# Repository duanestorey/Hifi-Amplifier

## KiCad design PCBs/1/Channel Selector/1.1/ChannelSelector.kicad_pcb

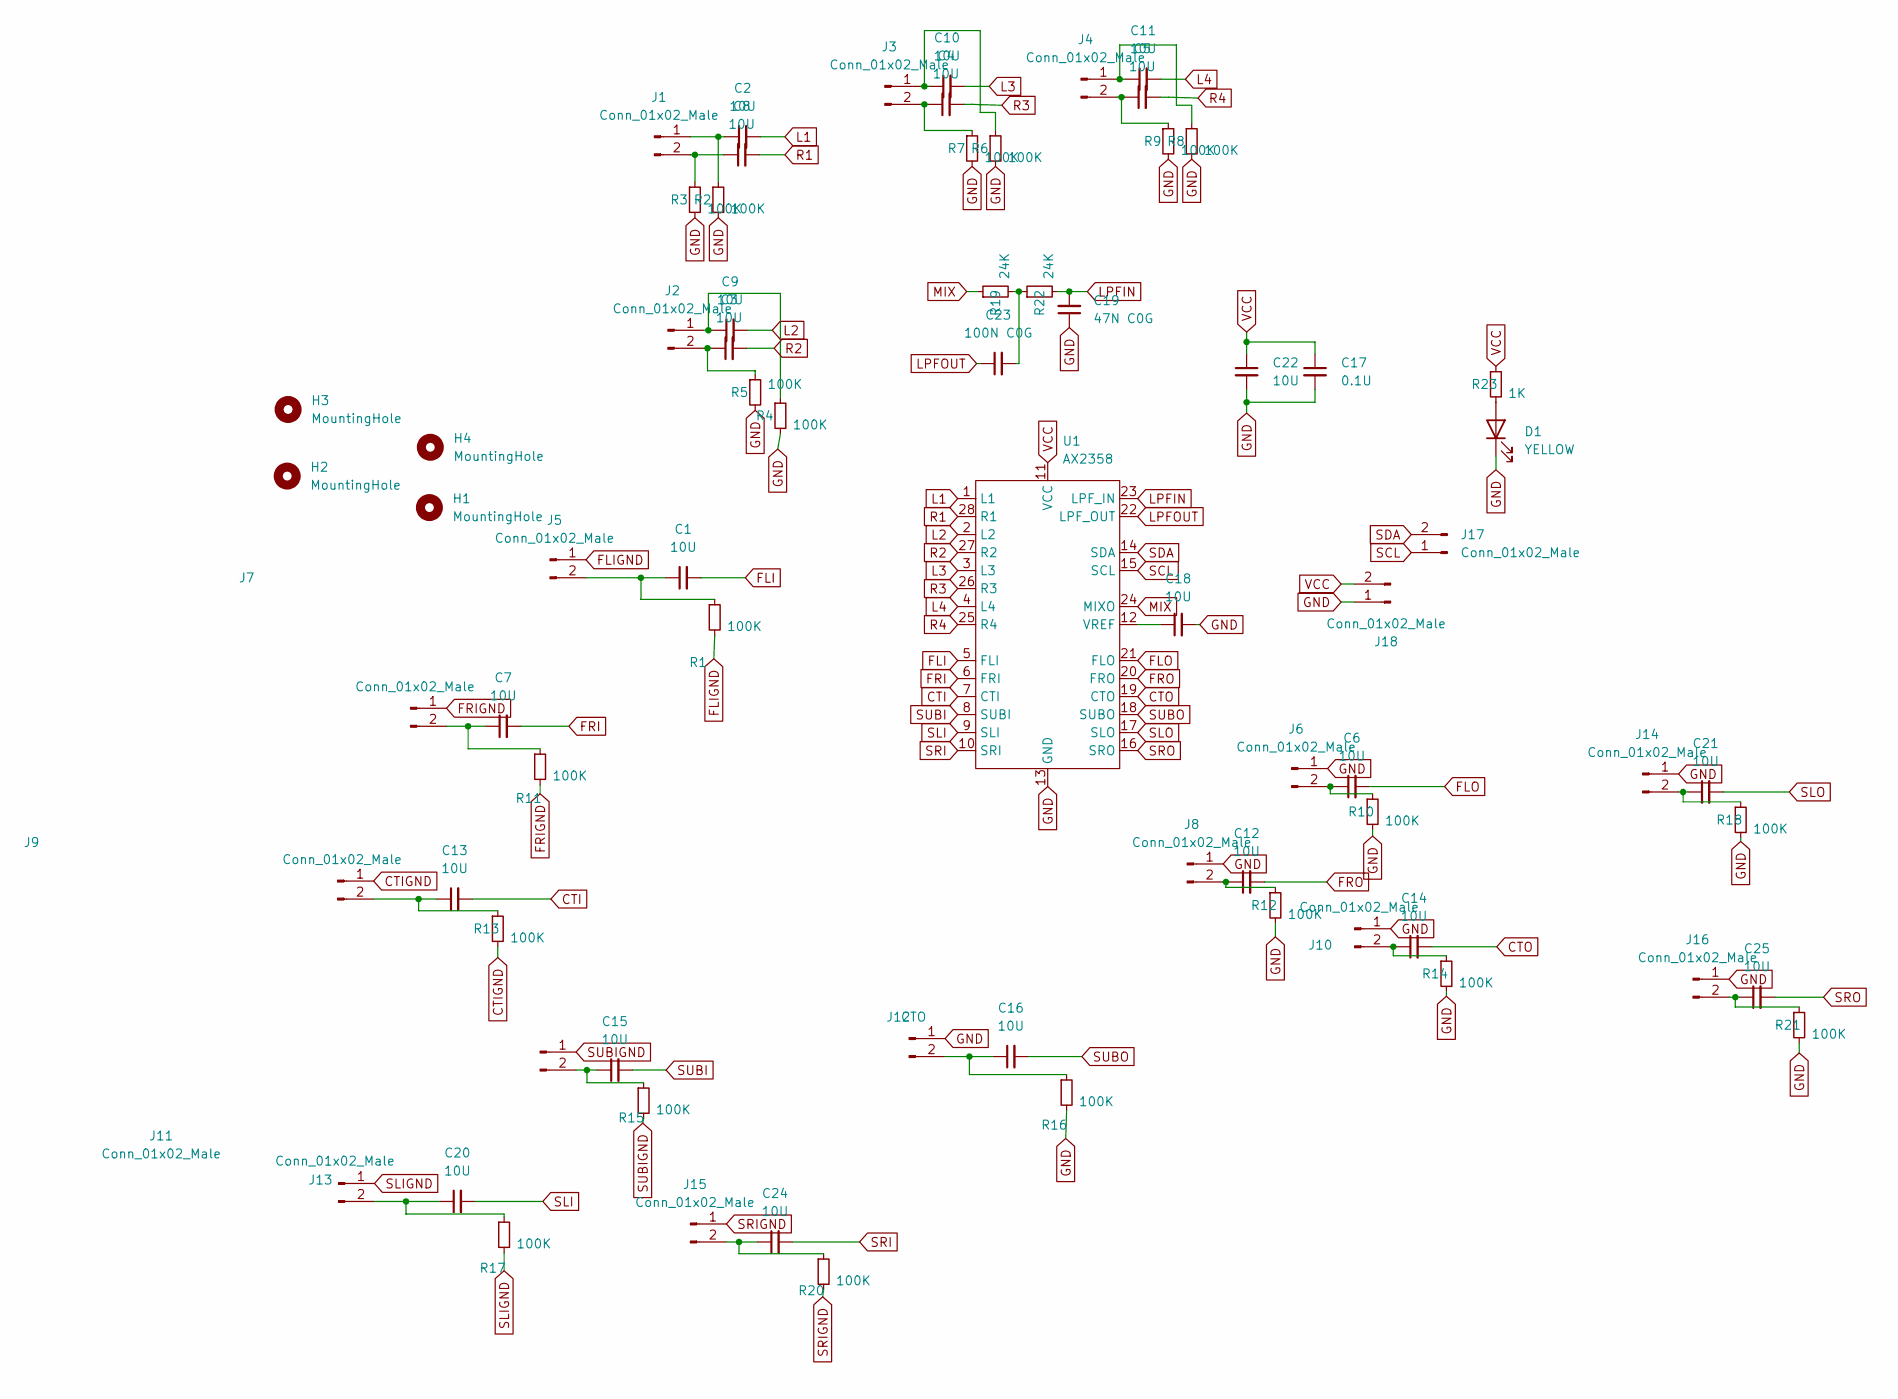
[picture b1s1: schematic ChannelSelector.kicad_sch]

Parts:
C1, C2, C3, C4, C5, C6, C7, C8, C9, C10, C11, C12, C13, C14, C15, C16, C20, C21, C24, C25: 10U; CP_Radial_D5.0mm_P2.50mm
C17: 0.1U; C_0805_2012Metric_Pad1.18x1.45mm_HandSolder
C18, C22: 10U; C_1206_3216Metric_Pad1.33x1.80mm_HandSolder
C19: 47N C0G; C_1206_3216Metric_Pad1.33x1.80mm_HandSolder
C23: 100N C0G; C_1206_3216Metric_Pad1.33x1.80mm_HandSolder
D1: YELLOW; LED_0805_2012Metric_Pad1.15x1.40mm_HandSolder
H1, H2, H3, H4: MountingHole; MountingHole_3.2mm_M3
J1, J2, J3, J4, J5, J6, J7, J8, J9, J10, J11, J13, J14, J15, J16, J17, J18: Conn_01x02_Male; JST_PH_B2B-PH-K_1x02_P2.00mm_Vertical
J12: CTO; JST_PH_B2B-PH-K_1x02_P2.00mm_Vertical
R1, R2, R3, R4, R5, R6, R7, R8, R9, R10, R11, R12, R13, R14, R15, R16, R17, R18, R20, R21: 100K; R_0805_2012Metric_Pad1.20x1.40mm_HandSolder
R19, R22: 24K; R_0805_2012Metric_Pad1.20x1.40mm_HandSolder
R23: 1K; R_0603_1608Metric_Pad0.98x0.95mm_HandSolder
U1: AX2358; SOIC-28W_7.5x18.7mm_P1.27mm

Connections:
CTI: C13.2, U1.7 (CTI)
CTIGND: J9.1, R13.2
CTO: C14.2, U1.19 (CTO)
FLI: C1.2, U1.5 (FLI)
FLIGND: J5.1, R1.2
FLO: C6.2, U1.21 (FLO)
FRI: C7.2, U1.6 (FRI)
FRIGND: J7.1, R11.2
FRO: C12.2, U1.20 (FRO)
GND: C17.2, C18.2, C19.1, C22.2, D1.1 (K), J6.1, J8.1, J10.1, J12.1, J14.1, J16.1, J18.1, R2.2, R3.2, R4.2, R5.2, R6.2, R7.2, R8.2, R9.2, R10.2, R12.2, R14.2, R16.2, R18.2, R21.2, U1.13 (GND)
L1: C2.2, U1.1 (L1)
L2: C9.2, U1.2 (L2)
L3: C10.2, U1.3 (L3)
L4: C11.2, U1.4 (L4)
LPFIN: C19.2, R22.2, U1.23 (LPF_IN)
LPFOUT: C23.1, U1.22 (LPF_OUT)
MIX: R19.1, U1.24 (MIXO)
unnamed: C23.2, R19.2, R22.1
unnamed: D1.2 (A), R23.2
unnamed: C2.1, J1.1, R2.1
unnamed: C8.1, J1.2, R3.1
unnamed: C9.1, J2.1, R4.1
unnamed: C3.1, J2.2, R5.1
unnamed: C10.1, J3.1, R6.1
unnamed: C4.1, J3.2, R7.1
unnamed: C11.1, J4.1, R8.1
unnamed: C5.1, J4.2, R9.1
unnamed: C1.1, J5.2, R1.1
unnamed: C6.1, J6.2, R10.1
unnamed: C7.1, J7.2, R11.1
unnamed: C12.1, J8.2, R12.1
unnamed: C13.1, J9.2, R13.1
unnamed: C14.1, J10.2, R14.1
unnamed: C15.1, J11.2, R15.1
unnamed: C16.1, J12.2, R16.1
unnamed: C20.1, J13.2, R17.1
unnamed: C21.1, J14.2, R18.1
unnamed: C24.1, J15.2, R20.1
unnamed: C25.1, J16.2, R21.1
unnamed: C18.1, U1.12 (VREF)
R1: C8.2, U1.28 (R1)
R2: C3.2, U1.27 (R2)
R3: C4.2, U1.26 (R3)
R4: C5.2, U1.25 (R4)
SCL: J17.1, U1.15 (SCL)
SDA: J17.2, U1.14 (SDA)
SLI: C20.2, U1.9 (SLI)
SLIGND: J13.1, R17.2
SLO: C21.2, U1.17 (SLO)
SRI: C24.2, U1.10 (SRI)
SRIGND: J15.1, R20.2
SRO: C25.2, U1.16 (SRO)
SUBI: C15.2, U1.8 (SUBI)
SUBIGND: J11.1, R15.2
SUBO: C16.2, U1.18 (SUBO)
VCC: C17.1, C22.1, J18.2, R23.1, U1.11 (VCC)

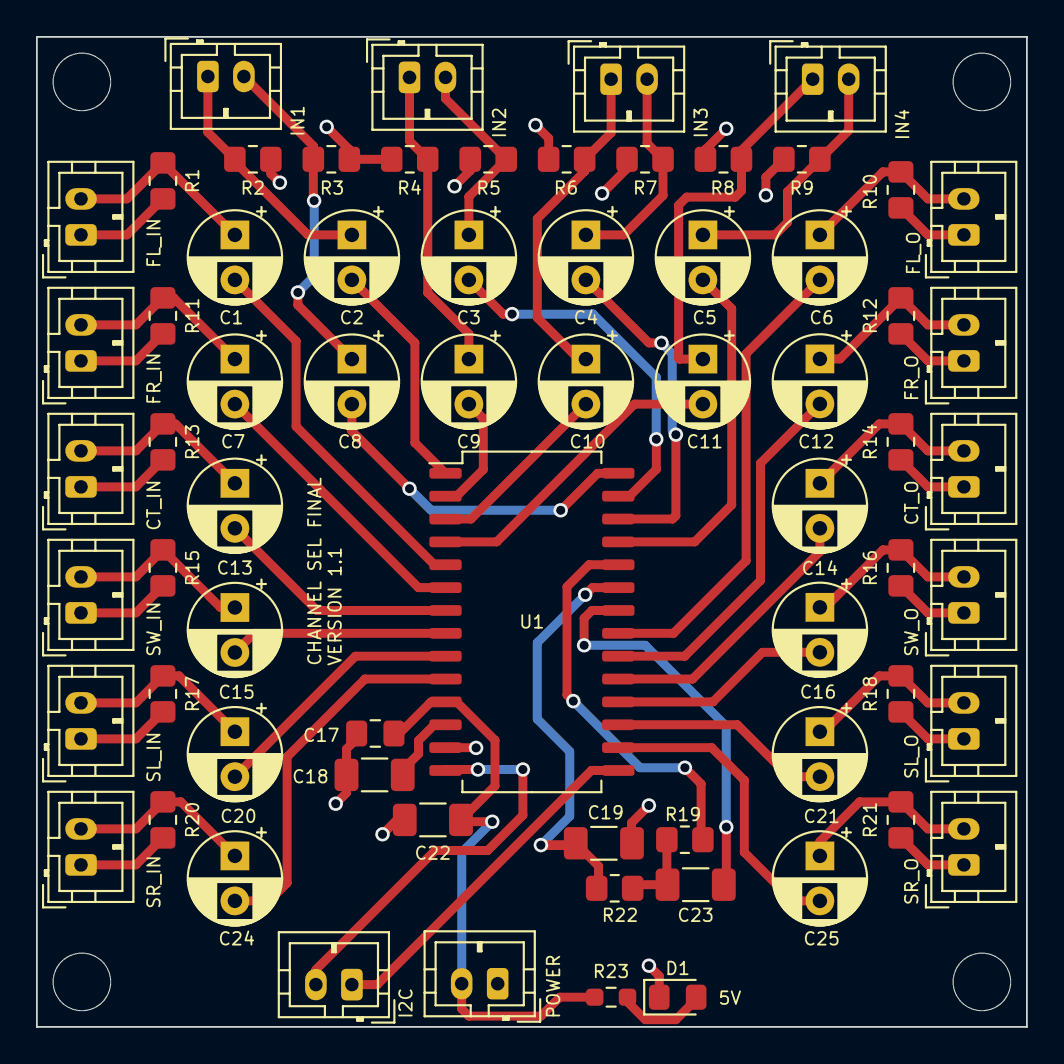
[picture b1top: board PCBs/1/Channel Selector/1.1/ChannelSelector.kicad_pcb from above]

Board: 2 copper layers, 55.0 x 55.0 mm, 72 parts (0 on the bottom side), 56 nets.

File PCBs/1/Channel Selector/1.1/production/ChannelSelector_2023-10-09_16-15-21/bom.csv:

Designator,Footprint,Quantity,Value,LCSC Part #
"C1, C10, C11, C12, C13, C14, C15, C16, C2, C20, C21, C24, C25, C3, C4, C5, C6, C7, C8, C9",CP_Radial_D5.0mm_P2.50mm,20,10U,
C17,0805,1,0.1U,
"C18, C22",1206,2,10U,
C19,1206,1,47N C0G,
C23,1206,1,100N C0G,
D1,0805,1,YELLOW,
"H1, H2, H3, H4",MountingHole_3.2mm_M3,4,MountingHole,
"J1, J10, J11, J13, J14, J15, J16, J17, J18, J2, J3, J4, J5, J6, J7, J8, J9",JST_PH_B2B-PH-K_1x02_P2.00mm_Vertical,17,Conn_01x02_Male,
J12,JST_PH_B2B-PH-K_1x02_P2.00mm_Vertical,1,CTO,
"R1, R10, R11, R12, R13, R14, R15, R16, R17, R18, R2, R20, R21, R3, R4, R5, R6, R7, R8, R9",0805,20,100K,
"R19, R22",0805,2,24K,
R23,0603,1,1K,
U1,SOIC-28W_7.5x18.7mm_P1.27mm,1,AX2358,

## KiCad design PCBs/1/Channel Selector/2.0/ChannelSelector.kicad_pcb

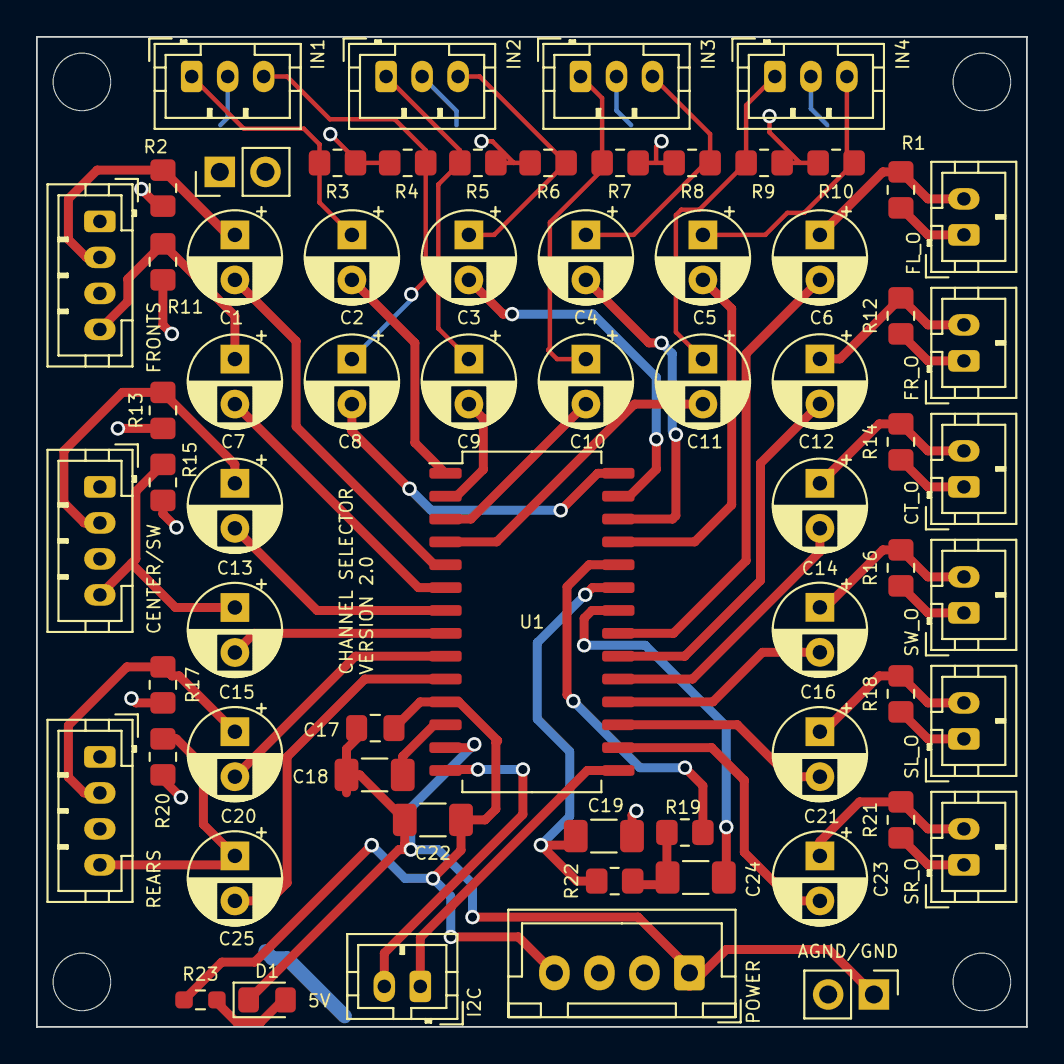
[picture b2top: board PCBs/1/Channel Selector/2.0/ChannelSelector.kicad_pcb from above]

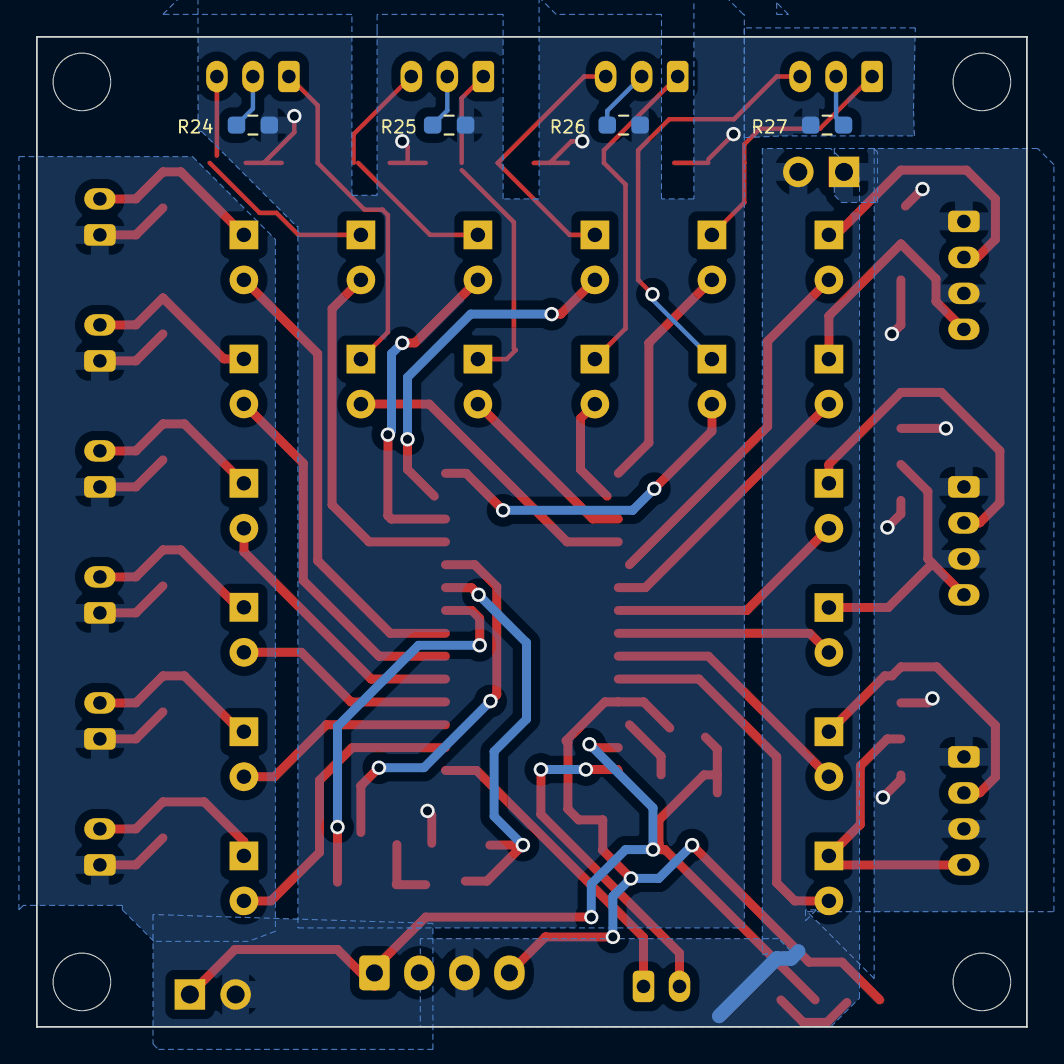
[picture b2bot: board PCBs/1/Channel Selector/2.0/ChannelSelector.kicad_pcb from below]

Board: 2 copper layers, 55.0 x 55.0 mm, 75 parts (4 on the bottom side), 56 nets.

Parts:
C1, C2, C3, C4, C5, C6, C7, C8, C9, C10, C11, C12, C13, C14, C15, C16, C20, C21, C23, C25: 10U; CP_Radial_D5.0mm_P2.50mm
C17: 0.1U; C_0805_2012Metric_Pad1.18x1.45mm_HandSolder
C18, C22: 10U; C_1206_3216Metric_Pad1.33x1.80mm_HandSolder
C19: 47N C0G; C_1206_3216Metric_Pad1.33x1.80mm_HandSolder
C24: 100N C0G; C_1206_3216Metric_Pad1.33x1.80mm_HandSolder
D1: YELLOW; LED_0805_2012Metric_Pad1.15x1.40mm_HandSolder
H1, H2, H3, H4: MountingHole; MountingHole_3.2mm_M3
J1, J2, J3, J4: Conn_01x03_Pin; JST_PH_B3B-PH-K_1x03_P2.00mm_Vertical
J5: Conn_01x02_Pin; PinHeader_1x02_P2.54mm_Vertical
J6: Conn_01x04_Pin; JST_XH_B4B-XH-A_1x04_P2.50mm_Vertical
J7, J9, J11, J15, J17, J19: Conn_01x02_Male; JST_PH_B2B-PH-K_1x02_P2.00mm_Vertical
J8, J10, J12: Conn_01x04_Pin; JST_PH_B4B-PH-K_1x04_P2.00mm_Vertical
J13: CTO; JST_PH_B2B-PH-K_1x02_P2.00mm_Vertical
J18: Conn_01x02_Socket; PinHeader_1x02_P2.54mm_Vertical
R1, R3, R4, R5, R6, R7, R8, R9, R10, R12, R14, R16, R18, R21: 100K; R_0805_2012Metric_Pad1.20x1.40mm_HandSolder
R2, R11, R13, R15, R17, R20: 10K; R_0805_2012Metric_Pad1.20x1.40mm_HandSolder
R19, R22: 24K; R_0805_2012Metric_Pad1.20x1.40mm_HandSolder
R23: 1K; R_0603_1608Metric_Pad0.98x0.95mm_HandSolder
R24, R25, R26, R27: 15R; R_0603_1608Metric_Pad0.98x0.95mm_HandSolder
U1: AX2358; SOIC-28W_7.5x18.7mm_P1.27mm

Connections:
5CHGND: J5.1, J8.1, J8.3, J10.1, J10.3, J12.1, J12.3, R2.2, R11.2, R13.2, R15.2, R17.2, R20.2
5V: C17.1, C22.1, J6.4, R23.1, U1.11 (VCC)
AGND: C19.1, J5.2, J6.3, J7.1, J9.1, J11.1, J13.1, J15.1, J17.1, J18.2, R1.2, R3.1, R4.2, R5.1, R6.2, R7.1, R8.2, R9.1, R10.2, R12.2, R14.2, R16.2, R18.2, R21.2, R24.1, R25.1, R26.1, R27.1
CTI: C13.2, U1.7 (CTI)
CTO: C14.2, U1.19 (CTO)
DAC_CT: C13.1, J10.2, R13.1
DAC_FL: C1.1, J8.2, R2.1
DAC_FR: C7.1, J8.4, R11.1
DAC_RL: C20.1, J12.2, R17.1
DAC_RR: C25.1, J12.4, R20.1
DAC_SW: C15.1, J10.4, R15.1
FLI: C1.2, U1.5 (FLI)
FLO: C6.2, U1.21 (FLO)
FRI: C7.2, U1.6 (FRI)
FRO: C12.2, U1.20 (FRO)
GND: C17.2, C18.2, C22.2, D1.1 (K), J6.1, J18.1, U1.13 (GND)
L1: C2.2, U1.1 (L1)
L2: C9.2, U1.2 (L2)
L3: C10.2, U1.3 (L3)
L4: C11.2, U1.4 (L4)
LPFIN: C19.2, R22.2, U1.23 (LPF_IN)
LPFOUT: C24.1, U1.22 (LPF_OUT)
MIX: R19.1, U1.24 (MIXO)
unnamed: C24.2, R19.2, R22.1
unnamed: D1.2 (A), R23.2
unnamed: C2.1, J1.1, R3.2
unnamed: J1.2, R27.2
unnamed: C8.1, J1.3, R4.1
unnamed: C9.1, J2.1, R5.2
unnamed: J2.2, R26.2
unnamed: C3.1, J2.3, R6.1
unnamed: C10.1, J3.1, R7.2
unnamed: J3.2, R25.2
unnamed: C4.1, J3.3, R8.1
unnamed: C11.1, J4.1, R9.2
unnamed: J4.2, R24.2
unnamed: C5.1, J4.3, R10.1
unnamed: C6.1, J7.2, R1.1
unnamed: C12.1, J9.2, R12.1
unnamed: C14.1, J11.2, R14.1
unnamed: C16.1, J13.2, R16.1
unnamed: C21.1, J15.2, R18.1
unnamed: C23.1, J17.2, R21.1
unnamed: C18.1, U1.12 (VREF)
R1: C8.2, U1.28 (R1)
R2: C3.2, U1.27 (R2)
R3: C4.2, U1.26 (R3)
R4: C5.2, U1.25 (R4)
SCL: J19.1, U1.15 (SCL)
SDA: J19.2, U1.14 (SDA)
SLI: C20.2, U1.9 (SLI)
SLO: C21.2, U1.17 (SLO)
SRI: C25.2, U1.10 (SRI)
SRO: C23.2, U1.16 (SRO)
SUBI: C15.2, U1.8 (SUBI)
SUBO: C16.2, U1.18 (SUBO)

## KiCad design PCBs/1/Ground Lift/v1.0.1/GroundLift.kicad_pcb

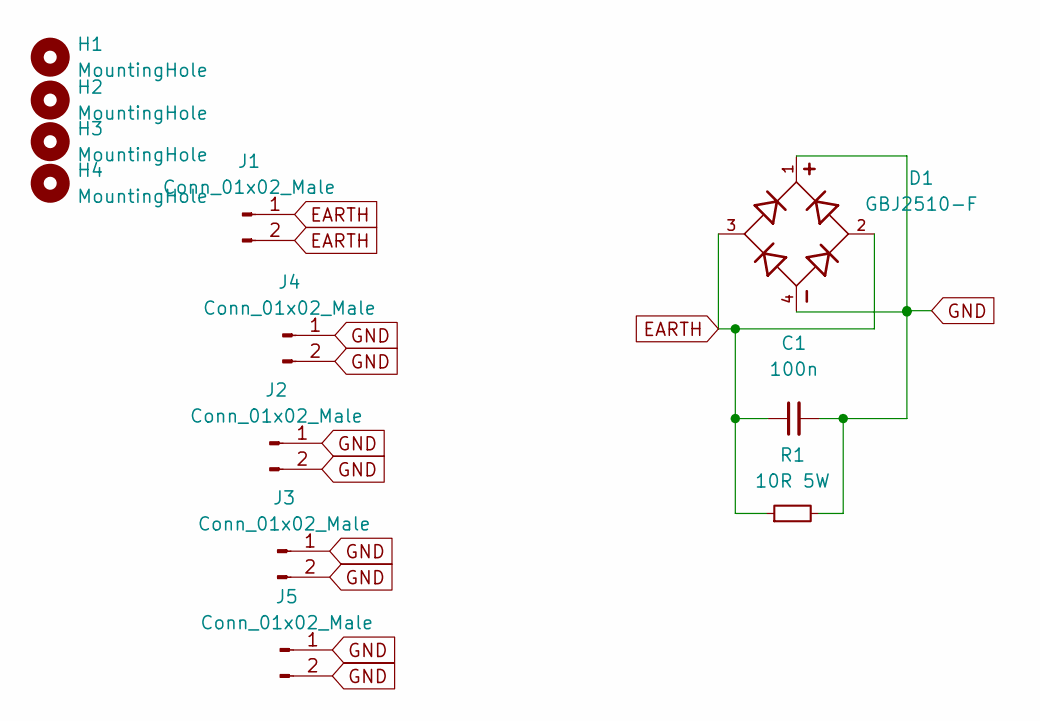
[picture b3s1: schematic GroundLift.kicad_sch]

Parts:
C1: 100n; C_Rect_L18.0mm_W5.0mm_P15.00mm_FKS3_FKP3
D1: GBJ2510-F; Diode_Bridge_19.0x19.0x6.8mm_P12.7mm
H1, H2, H3, H4: MountingHole; MountingHole_3.2mm_M3
J1: Conn_01x02_Male; JST_VH_B2P-VH-B_1x02_P3.96mm_Vertical
J2, J3, J4, J5: Conn_01x02_Male; TerminalBlock_Phoenix_MKDS-1,5-2-5.08_1x02_P5.08mm_Horizont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
R1: 10R 5W; R_Axial_Power_L25.0mm_W9.0mm_P27.94mm

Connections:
EARTH: C1.1, D1.2, D1.3, J1.1, J1.2, R1.1
GND: C1.2, D1.1, D1.4, J2.1, J2.2, J3.1, J3.2, J4.1, J4.2, J5.1, J5.2, R1.2

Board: 2 copper layers, 12 parts (0 on the bottom side), 2 nets, no tracks yet.

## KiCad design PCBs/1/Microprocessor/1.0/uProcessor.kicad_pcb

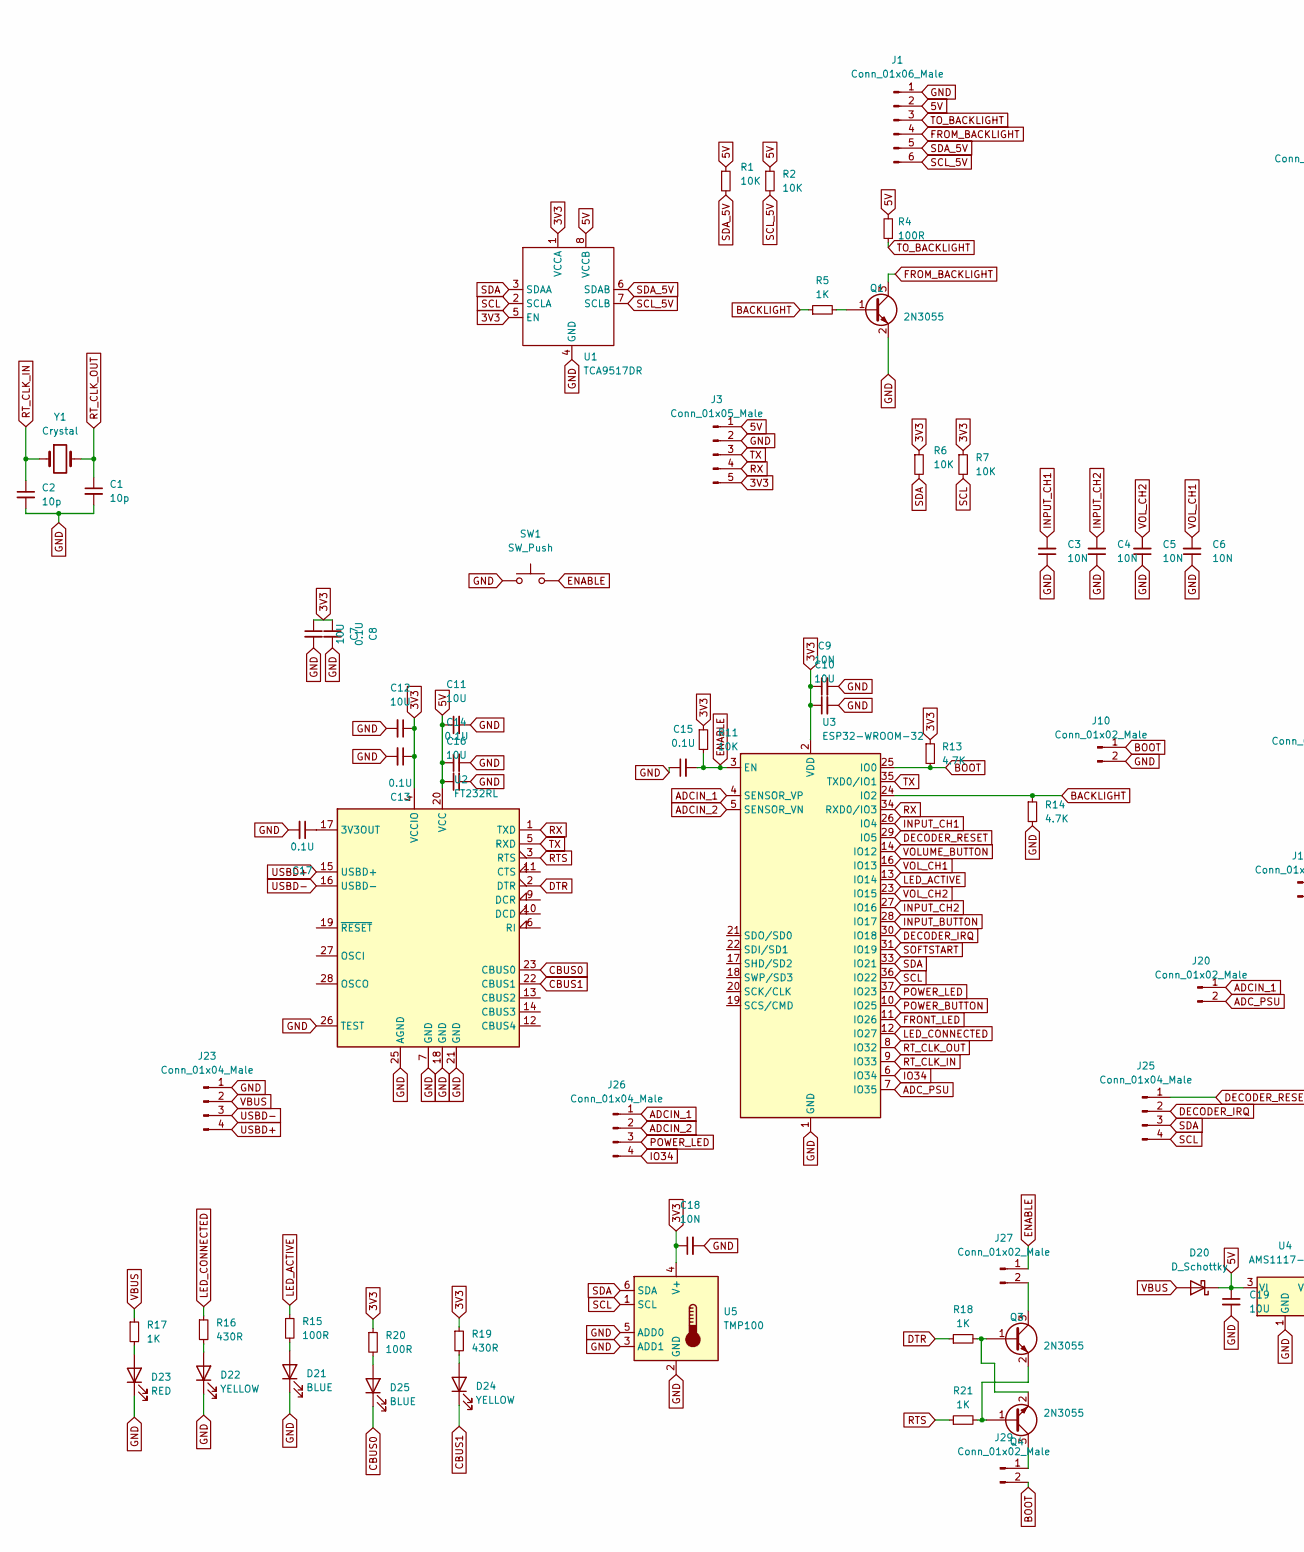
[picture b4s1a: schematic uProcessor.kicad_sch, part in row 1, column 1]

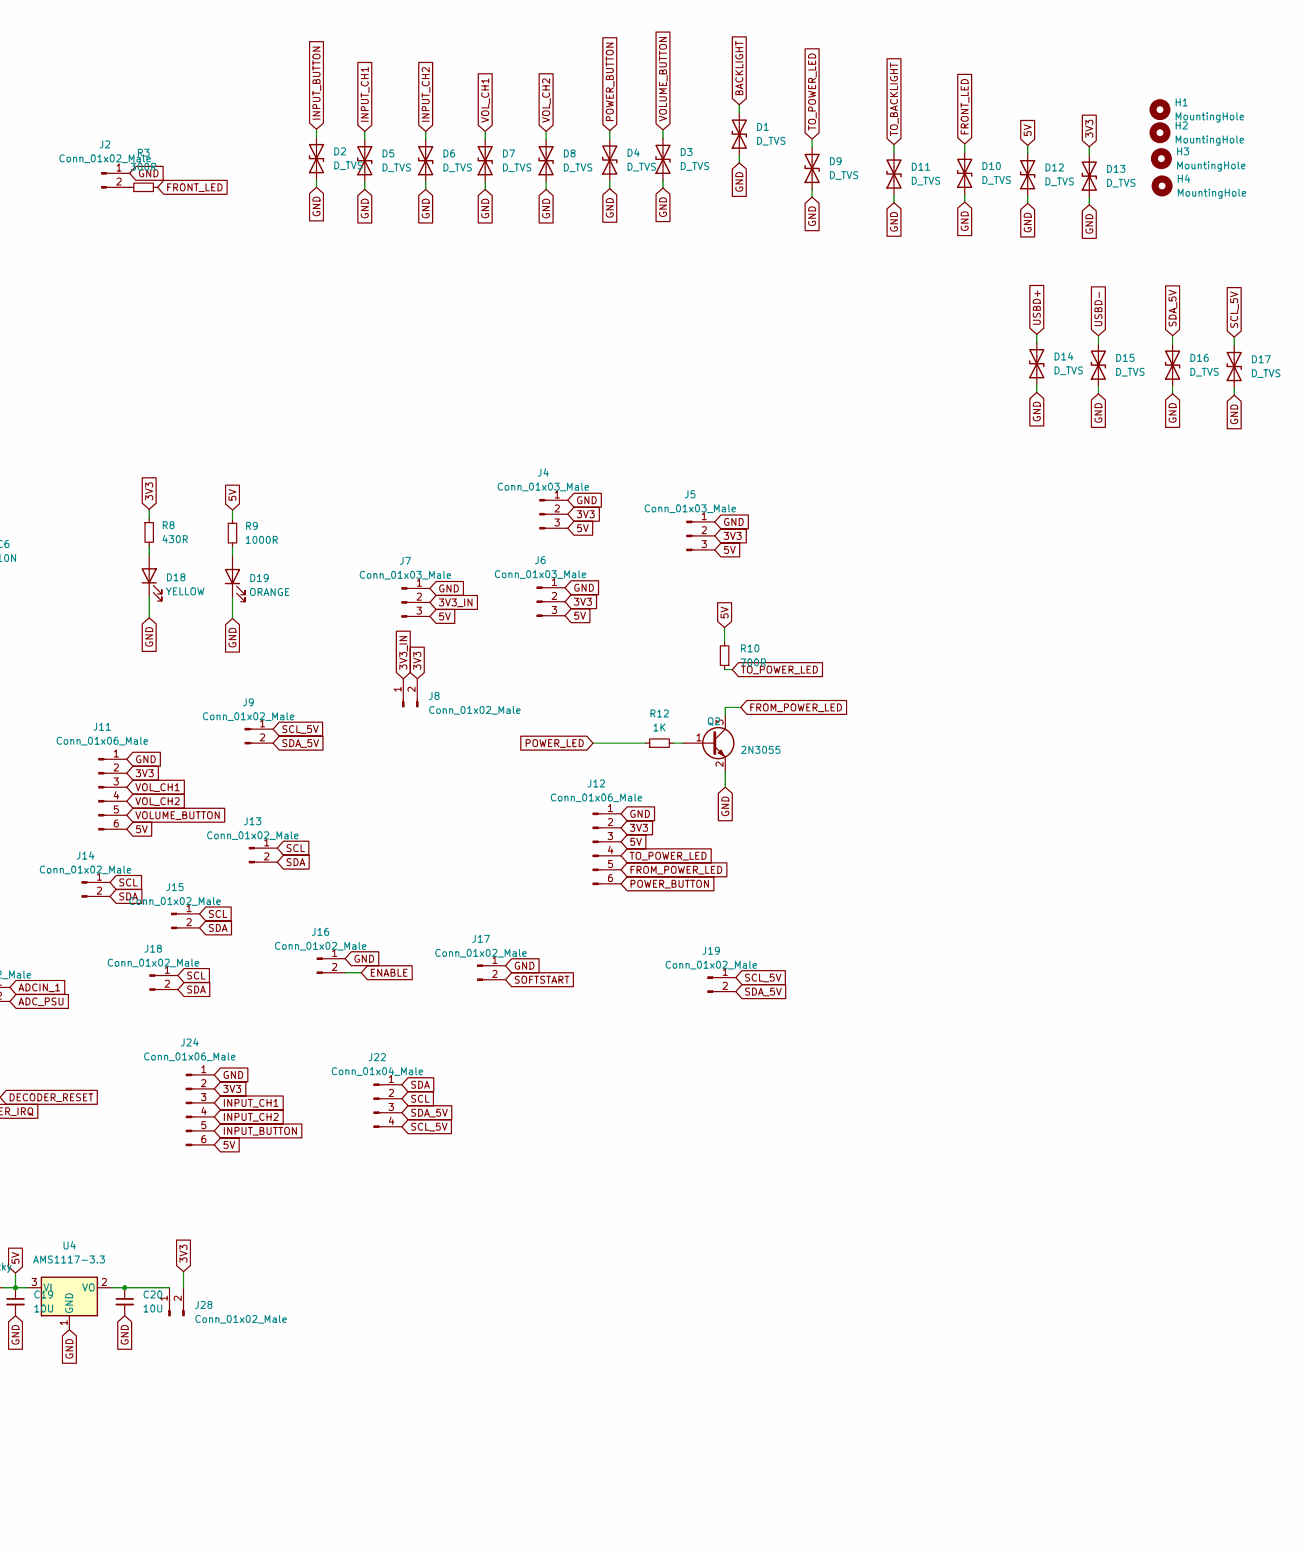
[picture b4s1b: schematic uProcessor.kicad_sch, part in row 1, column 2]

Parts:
C1, C2: 10p; C_0603_1608Metric_Pad1.08x0.95mm_HandSolder
C3, C4, C5, C6: 10N; C_0603_1608Metric_Pad1.08x0.95mm_HandSolder
C7, C10, C11, C12, C16, C19, C20: 10U; C_1206_3216Metric_Pad1.33x1.80mm_HandSolder
C8, C13, C14, C15, C17: 0.1U; C_0805_2012Metric_Pad1.18x1.45mm_HandSolder
C9, C18: 10N; C_0805_2012Metric_Pad1.18x1.45mm_HandSolder
D1, D2, D3, D4, D5, D6, D7, D8, D9, D10, D11, D12, D13, D14, D15, D16, D17: D_TVS; D_SOD-523
D18: YELLOW; LED_0805_2012Metric_Pad1.15x1.40mm_HandSolder; LCSC NCD0603R1
D19: ORANGE; LED_0805_2012Metric_Pad1.15x1.40mm_HandSolder; LCSC XL-1608UBC-04
D20: D_Schottky; D_SMA_Handsoldering
D21, D25: BLUE; LED_0805_2012Metric_Pad1.15x1.40mm_HandSolder; LCSC XL-1608UBC-04
D22, D24: YELLOW; LED_0805_2012Metric_Pad1.15x1.40mm_HandSolder; LCSC XL-1608UBC-04
D23: RED; LED_0805_2012Metric_Pad1.15x1.40mm_HandSolder; LCSC XL-1608UBC-04
H1, H2, H3, H4: MountingHole; MountingHole_3.2mm_M3
J1, J11, J12, J24: Conn_01x06_Male; JST_PH_B6B-PH-K_1x06_P2.00mm_Vertical
J2, J9, J13, J14, J15, J16, J17, J18, J19, J20: Conn_01x02_Male; JST_PH_B2B-PH-K_1x02_P2.00mm_Vertical
J3: Conn_01x05_Male; PinSocket_1x05_P2.54mm_Vertical
J4, J6: Conn_01x03_Male; PinHeader_1x03_P2.54mm_Vertical
J5, J7: Conn_01x03_Male; JST_PH_B3B-PH-K_1x03_P2.00mm_Vertical
J8, J10, J27, J28, J29: Conn_01x02_Male; PinHeader_1x02_P2.54mm_Vertical
J22, J26: Conn_01x04_Male; PinHeader_1x04_P2.54mm_Vertical
J23, J25: Conn_01x04_Male; JST_PH_B4B-PH-K_1x04_P2.00mm_Vertical
Q1, Q2, Q3, Q4: 2N3055; TSOT-23
R1, R2, R6, R7, R11: 10K; R_0603_1608Metric_Pad0.98x0.95mm_HandSolder
R3: 300R; R_0603_1608Metric_Pad0.98x0.95mm_HandSolder
R4, R15, R20: 100R; R_0603_1608Metric_Pad0.98x0.95mm_HandSolder
R5, R12, R17, R18, R21: 1K; R_0603_1608Metric_Pad0.98x0.95mm_HandSolder
R8, R16, R19: 430R; R_0603_1608Metric_Pad0.98x0.95mm_HandSolder
R9: 1000R; R_0603_1608Metric_Pad0.98x0.95mm_HandSolder
R10: 700R; R_0603_1608Metric_Pad0.98x0.95mm_HandSolder
R13, R14: 4.7K; R_0603_1608Metric_Pad0.98x0.95mm_HandSolder
SW1: SW_Push; Button Aliexpress 4x4
U1: TCA9517DR; SOIC-8_3.9x4.9mm_P1.27mm
U2: FT232RL; SSOP-28_5.3x10.2mm_P0.65mm
U3: ESP32-WROOM-32; ESP32-WROOM-32UE
U4: AMS1117-3.3; SOT-223-3_TabPin2
U5: TMP100; SOT-23-6
Y1: Crystal; Crystal_SMD_EuroQuartz_EQ161-2Pin_3.2x1.5mm_HandSoldering

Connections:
3V3: C7.1, C8.1, C9.1, C10.1, C12.1, C13.1, C18.1, D13.2 (A2), J3.5, J4.2, J5.2, J6.2, J8.2, J11.2, J12.2, J24.2, J28.2, R6.1, R7.1, R8.1, R11.1, R13.1, R19.1, R20.1, U1.1 (VCCA), U1.5 (EN), U2.4 (VCCIO), U3.2 (VDD), U5.4 (V+)
3V3_IN: J7.2, J8.1
5V: C11.1, C14.1, C16.1, C19.1, D12.2 (A2), D20.1 (K), J1.2, J3.1, J4.3, J5.3, J6.3, J7.3, J11.6, J12.3, J24.6, R1.1, R2.1, R4.2, R9.1, R10.2, U1.8 (VCCB), U2.20 (VCC), U4.3 (VI)
ADCIN_1: J20.1, J26.1, U3.4 (SENSOR_VP)
ADCIN_2: J26.2, U3.5 (SENSOR_VN)
ADC_PSU: J20.2, U3.7 (IO35)
BACKLIGHT: D1.2 (A2), R5.1, R14.1, U3.24 (IO2)
BOOT: J10.1, J29.2, R13.2, U3.25 (IO0)
CBUS0: D25.1 (K), U2.23 (CBUS0)
CBUS1: D24.1 (K), U2.22 (CBUS1)
DECODER_IRQ: J25.2, U3.30 (IO18)
DECODER_RESET: J25.1, U3.29 (IO5)
DTR: R18.1, U2.2 (DTR)
ENABLE: C15.2, J16.2, J27.1, R11.2, SW1.2, U3.3 (EN)
FROM_BACKLIGHT: J1.4, Q1.3 (C)
FROM_POWER_LED: J12.5, Q2.3 (C)
FRONT_LED: D10.2 (A2), R3.2, U3.11 (IO26)
GND: C1.2, C2.2, C3.1, C4.1, C5.1, C6.1, C7.2, C8.2, C9.2, C10.2, C11.2, C12.2, C13.2, C14.2, C15.1, C16.2, C17.2, C18.2, C19.2, C20.2, D1.1 (A1), D2.1 (A1), D3.1 (A1), D4.1 (A1), D5.1 (A1), D6.1 (A1), D7.1 (A1), D8.1 (A1), D9.1 (A1), D10.1 (A1), D11.1 (A1), D12.1 (A1), D13.1 (A1), D14.1 (A1), D15.1 (A1), D16.1 (A1), D17.1 (A1), D18.1 (K), D19.1 (K), D21.1 (K), D22.1 (K), D23.1 (K), J1.1, J2.1, J3.2, J4.1, J5.1, J6.1, J7.1, J10.2, J11.1, J12.1, J16.1, J17.1, J23.1, J24.1, Q1.2 (E), Q2.2 (E), R14.2, SW1.1, U1.4 (GND), U2.7 (GND), U2.18 (GND), U2.21 (GND), U2.25 (AGND), U2.26 (TEST), U3.1 (GND), U3.15 (GND), U3.38 (GND), U3.39 (GND), U4.1 (GND), U5.2 (GND), U5.3 (ADD1), U5.5 (ADD0)
INPUT_BUTTON: D2.2 (A2), J24.5, U3.28 (IO17)
INPUT_CH1: C3.2, D5.2 (A2), J24.3, U3.26 (IO4)
INPUT_CH2: C4.2, D6.2 (A2), J24.4, U3.27 (IO16)
IO34: J26.4, U3.6 (IO34)
LED_ACTIVE: R15.1, U3.13 (IO14)
LED_CONNECTED: R16.1, U3.12 (IO27)
unnamed: D18.2 (A), R8.2
unnamed: D19.2 (A), R9.2
unnamed: D21.2 (A), R15.2
unnamed: D22.2 (A), R16.2
unnamed: D23.2 (A), R17.2
unnamed: D24.2 (A), R19.2
unnamed: D25.2 (A), R20.2
unnamed: J2.2, R3.1
unnamed: J27.2, Q3.3 (C)
unnamed: C20.1, J28.1, U4.2 (VO)
unnamed: J29.1, Q4.3 (C)
unnamed: Q1.1 (B), R5.2
unnamed: Q2.1 (B), R12.2
unnamed: Q3.1 (B), Q4.2 (E), R18.2
unnamed: Q3.2 (E), Q4.1 (B), R21.2
unnamed: C17.1, U2.17 (3V3OUT)
POWER_BUTTON: D4.2 (A2), J12.6, U3.10 (IO25)
POWER_LED: J26.3, R12.1, U3.37 (IO23)
RTS: R21.1, U2.3 (RTS)
RT_CLK_IN: C2.1, U3.9 (IO33), Y1.1
RT_CLK_OUT: C1.1, U3.8 (IO32), Y1.2
RX: J3.4, U2.1 (TXD), U3.34 (RXD0/IO3)
SCL: J13.1, J14.1, J15.1, J18.1, J22.2, J25.4, R7.2, U1.2 (SCLA), U3.36 (IO22), U5.1 (SCL)
SCL_5V: D17.2 (A2), J1.6, J9.1, J19.1, J22.4, R2.2, U1.7 (SCLB)
SDA: J13.2, J14.2, J15.2, J18.2, J22.1, J25.3, R6.2, U1.3 (SDAA), U3.33 (IO21), U5.6 (SDA)
SDA_5V: D16.2 (A2), J1.5, J9.2, J19.2, J22.3, R1.2, U1.6 (SDAB)
SOFTSTART: J17.2, U3.31 (IO19)
TO_BACKLIGHT: D11.2 (A2), J1.3, R4.1
TO_POWER_LED: D9.2 (A2), J12.4, R10.1
TX: J3.3, U2.5 (RXD), U3.35 (TXD0/IO1)
USBD+: D14.2 (A2), J23.4, U2.15 (USBD+)
USBD-: D15.2 (A2), J23.3, U2.16 (USBD-)
VBUS: D20.2 (A), J23.2, R17.1
VOLUME_BUTTON: D3.2 (A2), J11.5, U3.14 (IO12)
VOL_CH1: C6.2, D7.2 (A2), J11.3, U3.16 (IO13)
VOL_CH2: C5.2, D8.2 (A2), J11.4, U3.23 (IO15)

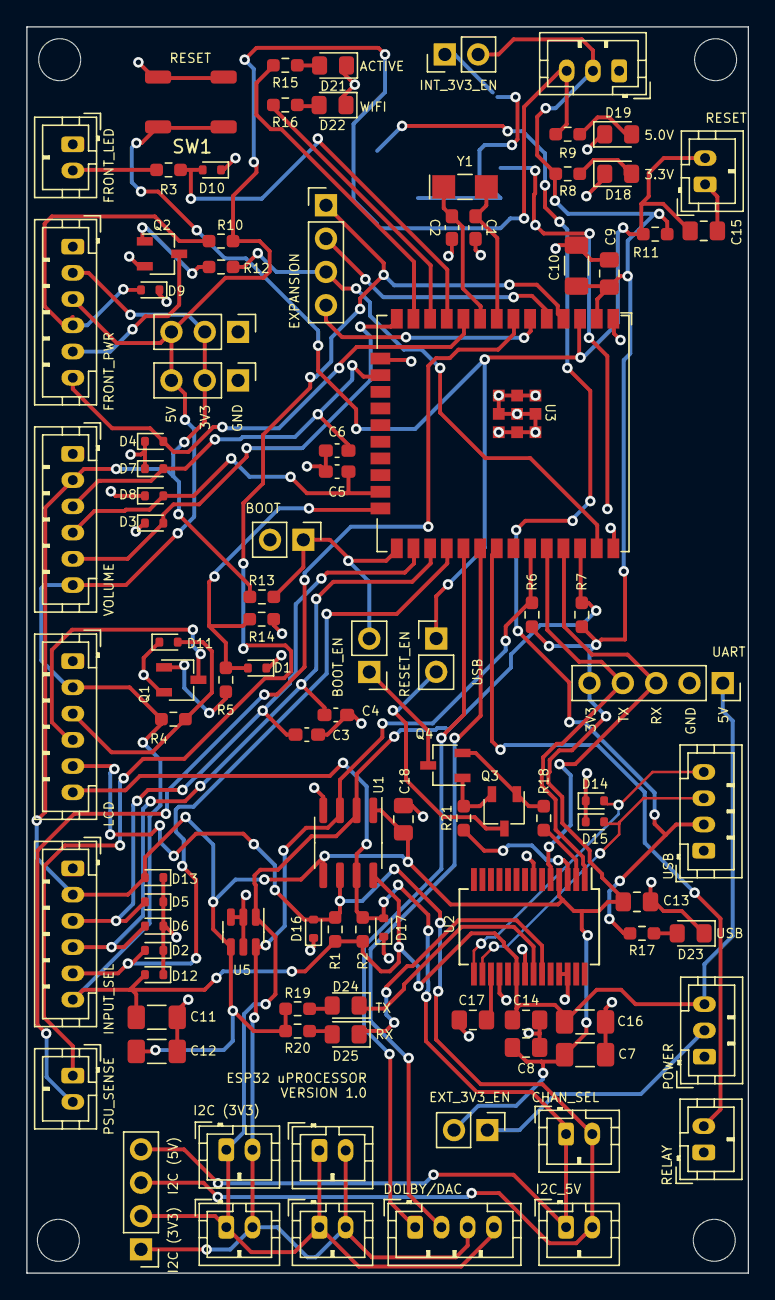
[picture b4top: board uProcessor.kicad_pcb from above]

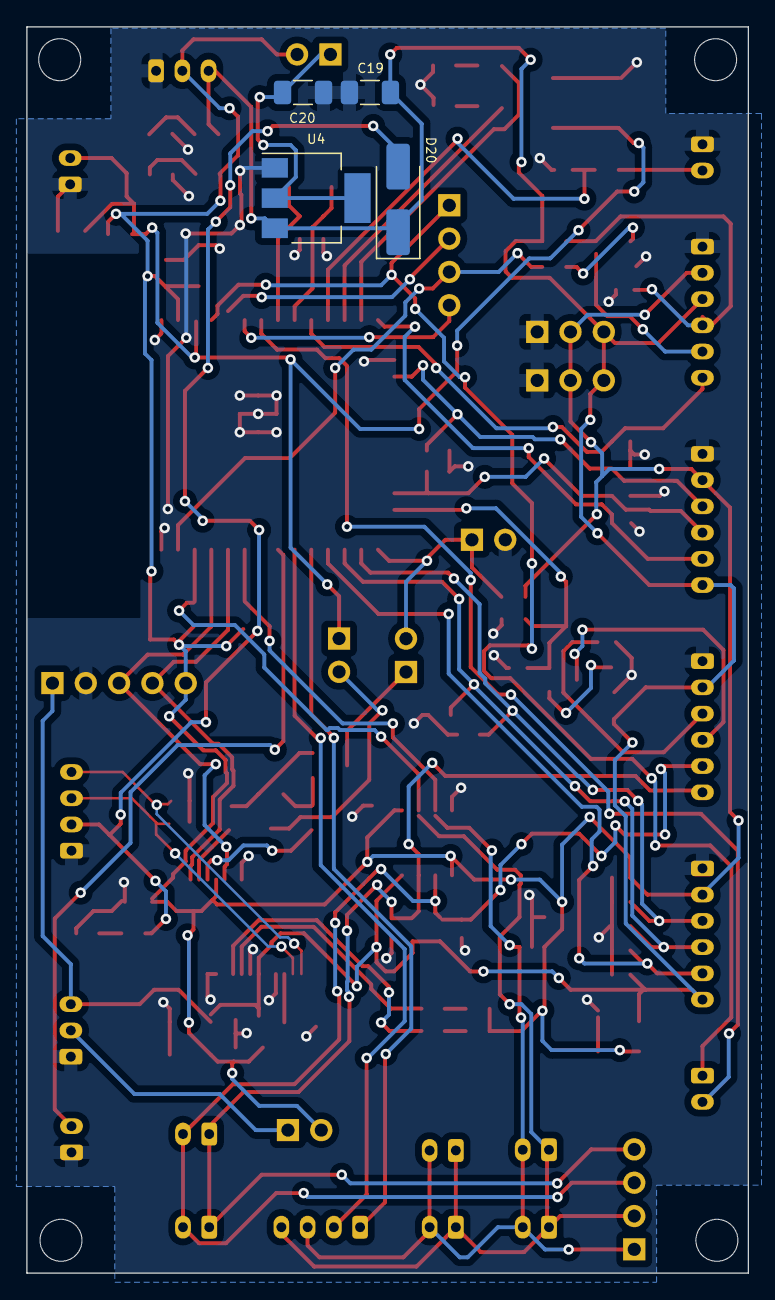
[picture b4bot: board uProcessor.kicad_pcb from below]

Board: 2 copper layers, 55.0 x 95.0 mm, 109 parts (4 on the bottom side), 60 nets.
